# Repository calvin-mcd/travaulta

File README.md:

# travaultas

The travaultas are a series of EC (topre) pcbs for mechvault's [Vault35](https://mechvault.net/products/vault-35-mini-keyboard) series designed by calvin0563. 

The series consists of the HHKB and WKL pcbs, both supporting a single bottomrow layout with the double 1.75u splitbars, and the Number/Macropad, supporting all layout options. 

Firmware source code and the OEM plate file are available in their respective folders. In order to fit the topre pcb into the case, small modifications to some housings are necessary. Please refer to the extensive build guide by cia\_moonchild in order to learn how to make the assembled pcb fit into the vault35 case.

[Build Guide!!!](https://imgur.com/a/L5vGjtF)

**BEWARE**: The HHKB pcb has been fully tested and confirmed to work. The WKL and Numpad have not yet been prototyped and still require firmware. 

## Layout

**HHKB**

[Link](http://www.keyboard-layout-editor.com/#/gists/d333b15956554a98cf3ed6f06e2de3bf)

**WKL**

[Link](https://www.keyboard-layout-editor.com/#/gists/da6e12de7bd5171aa8982730b8f45f17)

**NUMPAD**

## Images

## Firmware

The basic EC firmware is ready to go and the source code is provided for tweaking any settings.

## Plates & Hardware

The plate file is OEM housing (so original, deskey, klc, pbb housings should all work). Be sure to order the plate in 1.2mm thickness regardless of material.

Furthermore, you will need 17x 10mm M2 screws and M2 nuts to assemble the HHKB and WKL pcbs. And 6x 10mm M2 screws and nuts to assemble numbpad.

## Disclaimer

1) Please proceed with caution with respect to copyright issues when using this repository
2) Take note that this is strictly for non-commercial use only
3) This PCB has been fully tested and confirmed to work. The members of the PCB development team are however not liable if you end up with a non-functional pcb. Order at your own risk. Support will not be provided but pull requests will be reviewed and possibly accepted.

## License

Shield: 

This work is licensed under a  
[Creative Commons Attribution-NonCommercial-ShareAlike 4.0 International License](http://creativecommons.org/licenses/by-nc-sa/4.0/).

## Credits

big thanks go out to Cain both for the inspiration and the support! My topre work is heavily lifted of Cipulot\#8455's open source work. I could not have done it without these resources. So I want to thank both cipulot and matthewdias\#2671 for their direct input, feedback and help along the way. Much much appreciated!

So many other thanks to go around, I fear I will forget people. There is Ciantha with their amazing guide! A whole bunch of early supporters that made the proto order possible. The keyboard Atelier discord for support. ssbb\#9052 with help with the firmware! And finally Alas/Sofia who decided to get a first GB for this on its feet!!

Any questions, contact Calvin0563 on Discord.

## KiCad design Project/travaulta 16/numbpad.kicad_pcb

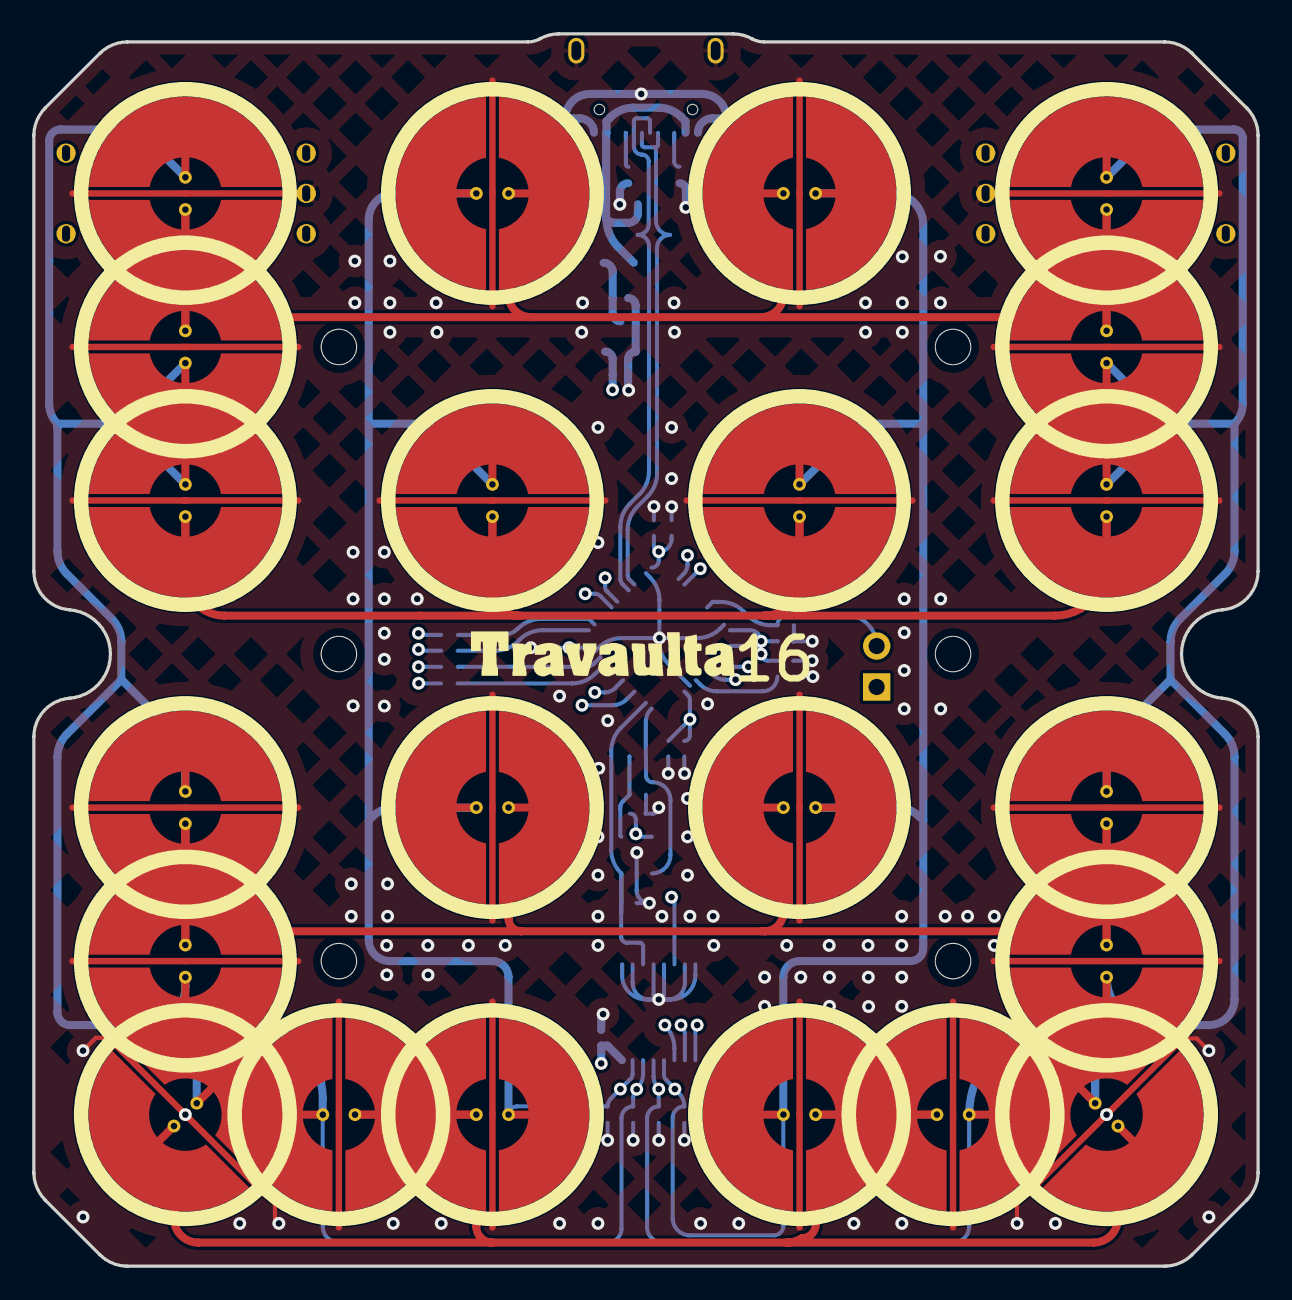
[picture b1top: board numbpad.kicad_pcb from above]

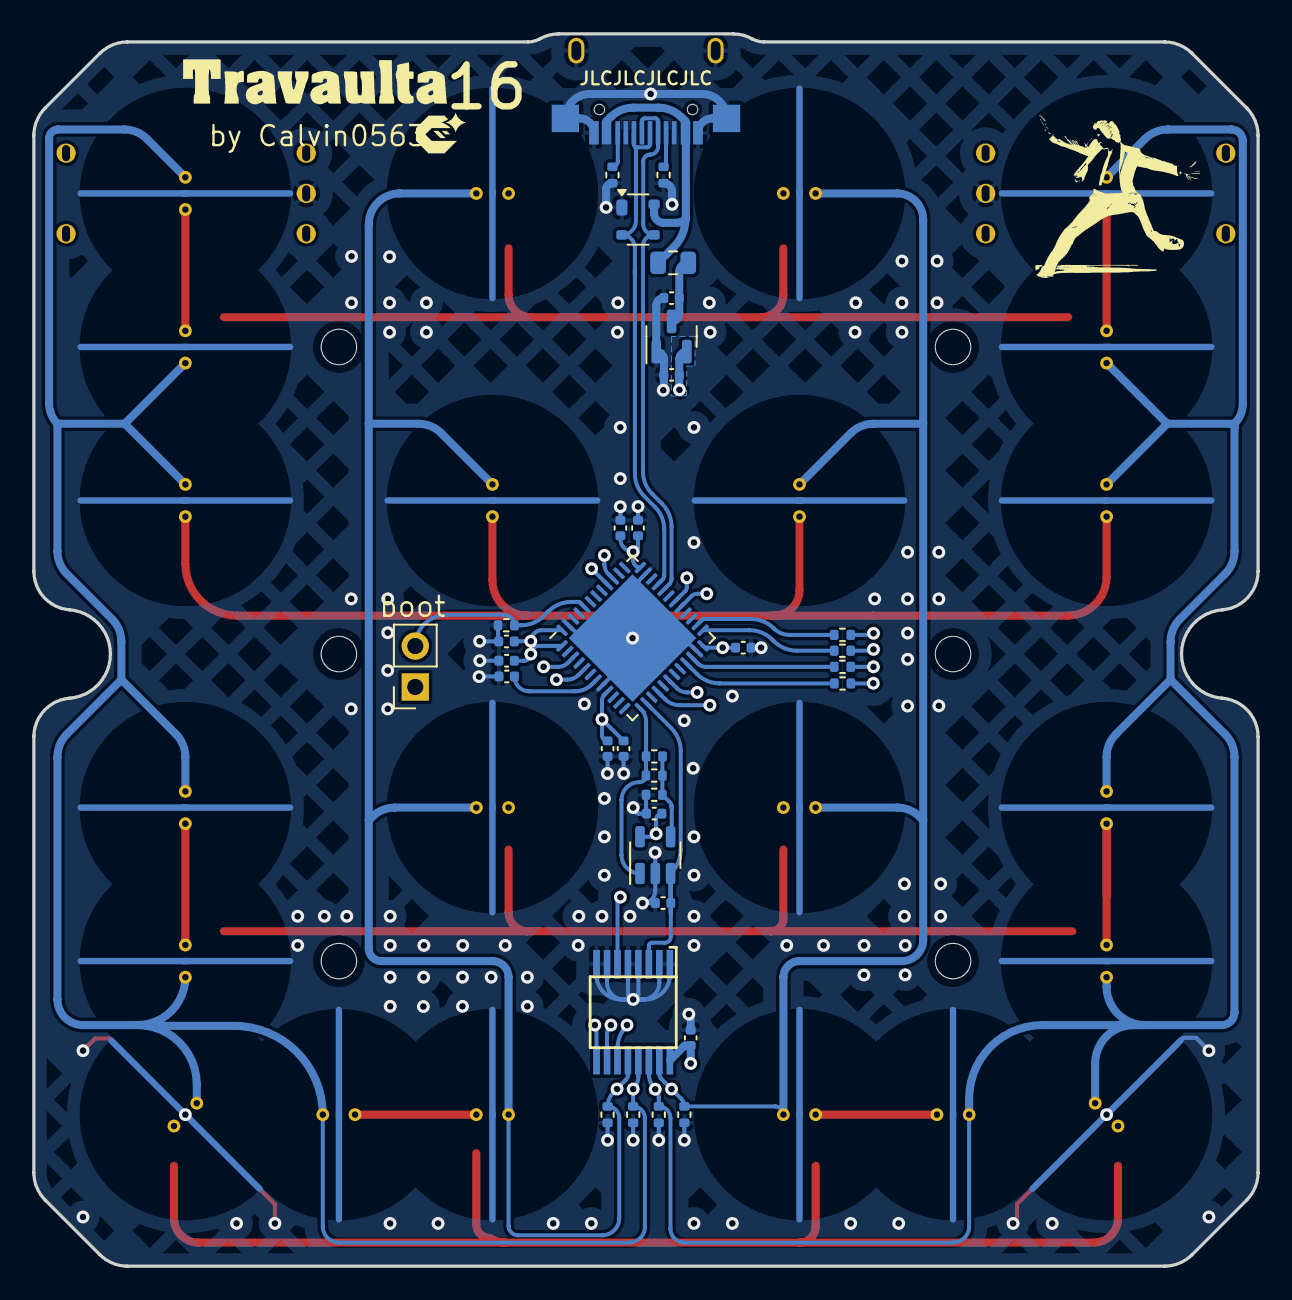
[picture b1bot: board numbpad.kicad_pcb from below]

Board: 4 copper layers, 76.0 x 76.5 mm, 63 parts (41 on the bottom side), 33 nets.

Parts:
C1, C2, C3, C4, C5, C7: 100nf; C_0402_1005Metric
C6: 10uF; C_0402_1005Metric
C8: 1uF; C_0402_1005Metric
C9, C10: 100nF; C_0402_1005Metric
C11: 220pF NP0; C_0402_1005Metric
C_LDO1, C_LDO2: 1uF; C_0402_1005Metric
F1: 500mA; Fuse_0805_2012Metric
H1, H2, H3, H4, H5, H6: MountingHole; HOLE_M2
R1: 10k; R_0402_1005Metric
R2, R3, R4, R5: 100; R_0402_1005Metric
R6, R7, R8, R9, R11: 100k; R_0402_1005Metric
R12: 1k; R_0402_1005Metric
R13: DNP; R_0402_1005Metric
R_USB1, R_USB2: 5.1k; R_0402_1005Metric
SW1, SW2, SW3, SW4, SW5, SW6, SW7, SW8, SW9, SW10, SW11, SW12, SW13, SW14, SW15, SW16, SW18, SW19, SW21, SW22: EC_SW; ecs_pad_1U_no_ring
SW17: SKQGABE010; PinSocket_1x02_P2.54mm_Vertical
SW20, SW23: EC_SW_RotaryEncoder_Switch; ecs_pad_1U_no_ring_rotary_encoder_ec12
U1: STM32F072CBUx; QFN-48-1EP_7x7mm_P0.5mm_EP5.6x5.6mm
U2: PRTR5V0U2X; SOT-143
U3: XC6206PxxxMR; SOT-23
U4: 74HC4051; TSSOP16
U5: OPA354; SOT-23-5
USB1: HRO-TYPE-C-31-M-12; XUNPU-TYPEC-312DSS-ACP16-Assembly

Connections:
+3V3: C2.1, C3.1, C4.1, C5.1, C6.1, C7.1, C8.1, C9.2, C10.2, C_LDO2.1, SW17.1, U1.1 (VBAT), U1.9 (VDDA), U1.24 (VDD), U1.36 (VDDIO2), U1.48 (VDD), U3.2 (VO), U4.16 (VCC), U5.5 (V+)
+5V: C_LDO1.1, F1.2, U3.3 (VI)
ADC: R11.1, R13.1, U1.13 (PA3), U5.1
AMUX_SEL_0: U1.16 (PA6), U4.11 (S0)
AMUX_SEL_1: U1.18 (PB0), U4.10 (S1)
AMUX_SEL_2: U1.3 (PC14), U4.9 (S2)
APLEX_EN_PIN_0: U1.5 (PF0), U4.6 (~E)
APLEX_OUT: C11.1, U1.14 (PA4), U4.3 (A), U5.3 (+)
BOOT0: R1.1, SW17.2, U1.44 (BOOT0)
Col 0: R8.1, SW1.1, SW5.1, SW9.1, SW13.1, SW18.1, SW20.2, SW22.1, U4.14 (A1)
Col 1: R6.1, SW2.1, SW6.1, SW10.1, SW14.1, U4.15 (A2)
Col 2: R9.1, SW3.1, SW7.1, SW11.1, SW15.1, U4.12 (A3)
Col 3: R7.1, SW4.1, SW8.1, SW12.1, SW16.1, SW19.1, SW21.1, SW23.1, U4.13 (A0)
D+: U1.33 (PA12), U2.2 (I/O1), USB1.6 (DP1), USB1.8 (DP2)
D-: U1.32 (PA11), U2.3 (I/O2), USB1.5 (DN2), USB1.7 (DN1)
GND: C1.2, C2.2, C3.2, C4.2, C5.2, C6.2, C7.2, C8.2, C9.1, C10.1, C11.2, C_LDO1.2, C_LDO2.2, R1.2, R6.2, R7.2, R8.2, R9.2, R12.2, R_USB1.2, R_USB2.2, SW1.3 (SG), SW2.3 (SG), SW3.3 (SG), SW4.3 (SG), SW5.3 (SG), SW6.3 (SG), SW7.3 (SG), SW8.3 (SG), SW9.3 (SG), SW10.3 (SG), SW11.3 (SG), SW12.3 (SG), SW13.3 (SG), SW14.3 (SG), SW15.3 (SG), SW16.3 (SG), SW18.3 (SG), SW19.3 (SG), SW20.3, SW20.C, SW21.3 (SG), SW22.3 (SG), SW23.3, SW23.C, U1.8 (VSSA), U1.23 (VSS), U1.35 (VSS), U1.47 (VSS), U1.49 (VSS), U2.1 (GND), U3.1 (GND), U4.1 (A4), U4.2 (A6), U4.4 (A7), U4.5 (A5), U4.7 (VEE), U4.8 (GND), U5.2 (V-), USB1.1 (GND), USB1.12 (GND), USB1.13 (SHIELD)
NRST: C1.1, U1.7 (NRST)
unnamed: R3.1, U1.21 (PB10)
unnamed: R2.1, U1.22 (PB11)
unnamed: R4.1, U1.25 (PB12)
unnamed: R5.1, U1.26 (PB13)
unnamed: R11.2, R12.1, R13.2, U5.4 (-)
unnamed: R_USB1.1, USB1.4 (CC1)
unnamed: R_USB2.1, USB1.10 (CC2)
Row 0: R4.2, SW2.2, SW3.2, SW18.2, SW19.2, SW20.1, SW23.2
Row 1: R5.2, SW5.2, SW6.2, SW7.2, SW8.2
Row 2: R2.2, SW1.2, SW9.2, SW10.2, SW11.2, SW12.2, SW21.2
Row 3: R3.2, SW4.2, SW13.2, SW14.2, SW15.2, SW16.2, SW22.2
VCC: F1.1, U2.4 (VCC), USB1.2 (VBUS), USB1.11 (VBUS)
rotA: SW20.A, U1.30 (PA9)
rotB: SW20.B, U1.29 (PA8)
rotC: SW23.A, U1.39 (PB3)
rotD: SW23.B, U1.40 (PB4)

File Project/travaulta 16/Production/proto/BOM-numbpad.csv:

Comment,Designator,Footprint,LCSC
1k,R12,R_0402_1005Metric,C11702
OPA354,U5,SOT-23-5,C13388
220pF NP0,C11,C_0402_1005Metric,C1530
100,"R2,R3,R4,R5",R_0402_1005Metric,C25076
100k,"R11,R6,R7,R8,R9",R_0402_1005Metric,C25741
10k,R1,R_0402_1005Metric,C25744
5.1k,"R_USB1,R_USB2",R_0402_1005Metric,C25905
PRTR5V0U2X,U2,SOT-143,C2827688
500mA,F1,Fuse_0805_2012Metric,C2833485
HRO-TYPE-C-31-M-12,USB1,XUNPU-TYPEC-312DSS-ACP16-Assembly,C2909601
100nf,"C1,C10,C2,C3,C4,C5,C7,C9",C_0402_1005Metric,C307331
10uF,C6,C_0402_1005Metric,C315248
1uF,"C8,C_LDO1,C_LDO2",C_0402_1005Metric,C52923
XC6206PxxxMR,U3,SOT-23,C5446
74HC4051,U4,TSSOP16,C5645
STM32F072CBUx,U1,QFN-48-1EP_7x7mm_P0.5mm_EP5.6x5.6mm,C92504

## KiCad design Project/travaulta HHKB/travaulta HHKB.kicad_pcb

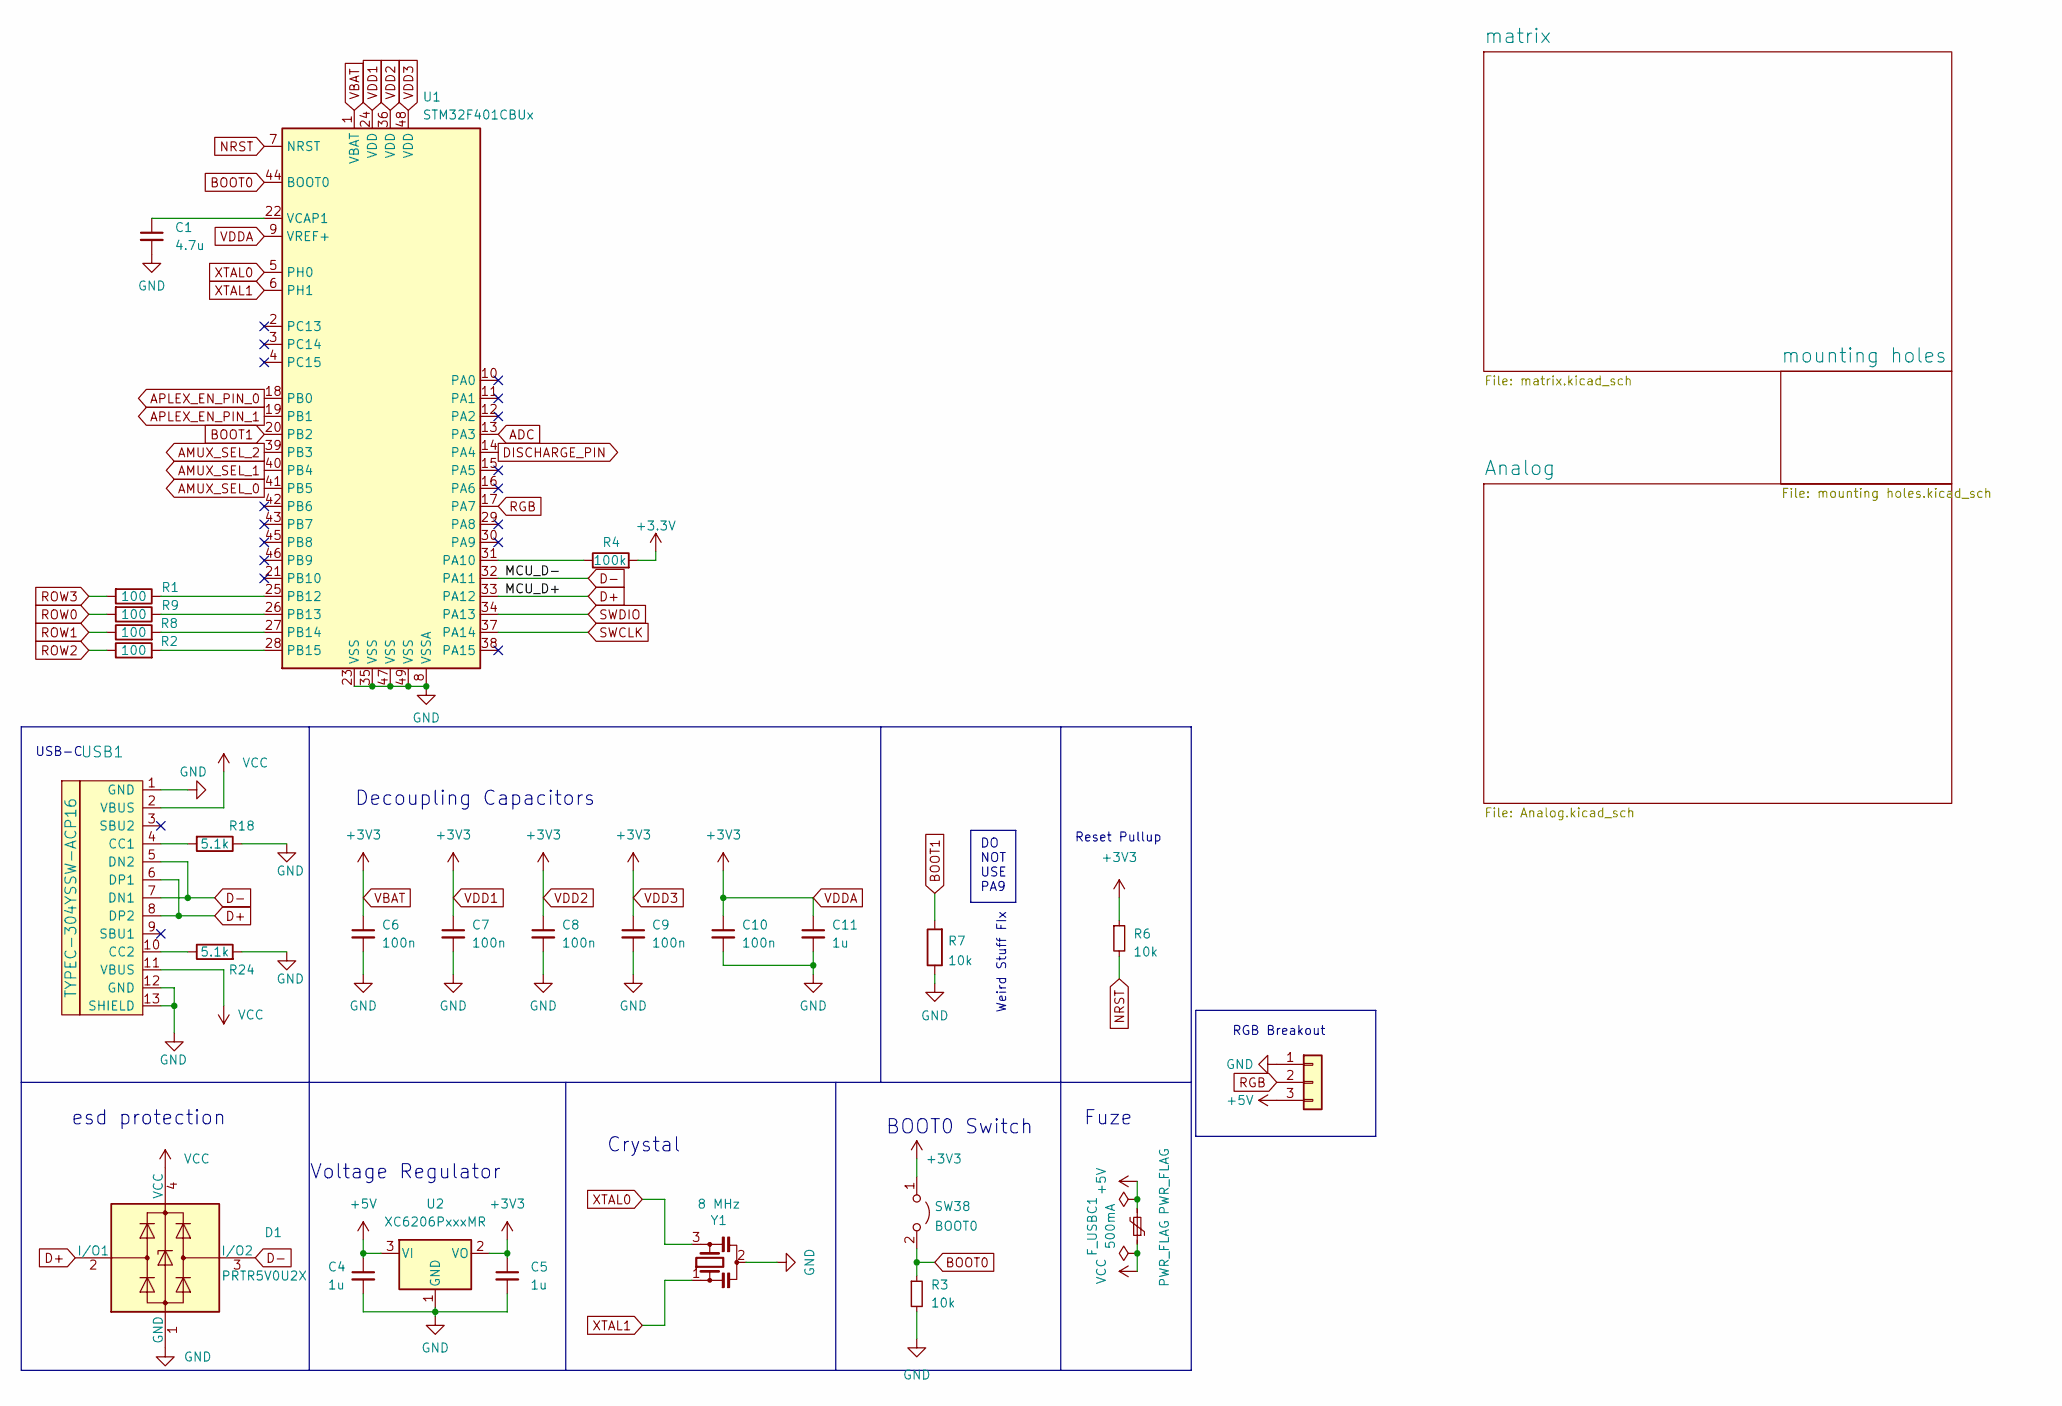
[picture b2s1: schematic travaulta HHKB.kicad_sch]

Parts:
C1: 4.7u; C_0402_1005Metric
C4, C5, C11: 1u; C_0402_1005Metric
C6, C7, C8, C9, C10: 100n; C_0402_1005Metric
D1: PRTR5V0U2X; SOT-143
F_USBC1: 500mA; Fuse_1206_3216Metric
J5: ARGB; PinHeader_1x03_P1.27mm_Vertical
R1, R2, R8, R9: 100; R_0402_1005Metric; LCSC C25076
R3, R6: 10k; R_0402_1005Metric
R4: 100k; R_0402_1005Metric; LCSC C25741
R7: 10k; R_0402_1005Metric; LCSC C25744
R18, R24: 5.1k; R_0402_1005Metric; LCSC C25905
SW38: BOOT0; PinHeader_1x02_P2.54mm_Vertical
U1: STM32F401CBUx; QFN-48-1EP_7x7mm_P0.5mm_EP5.6x5.6mm; LCSC C118825
U2: XC6206PxxxMR; SOT-23
USB1: TYPEC-304YSSW-ACP16; LCSC C2840392
Y1: 8 MHz; Resonator_SMD_Murata_CSTxExxV-3Pin_3.0x1.1mm; LCSC C907975

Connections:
+5V: C4.1, F_USBC1.2, U2.3 (VI); also elsewhere on the board
ADC: U1.13 (PA3); also elsewhere on the board
AMUX_SEL_0: U1.41 (PB5); also elsewhere on the board
AMUX_SEL_1: U1.40 (PB4); also elsewhere on the board
AMUX_SEL_2: U1.39 (PB3); also elsewhere on the board
APLEX_EN_PIN_0: U1.18 (PB0); also elsewhere on the board
APLEX_EN_PIN_1: U1.19 (PB1); also elsewhere on the board
APLEX_OUT_PIN_0: U1.14 (PA4); also elsewhere on the board
BOOT0: R3.1, SW38.2 (B), U1.44 (BOOT0)
BOOT1: R7.2, U1.20 (PB2)
D+: D1.2 (I/O1), U1.33 (PA12), USB1.6 (DP1), USB1.8 (DP2)
D-: D1.3 (I/O2), U1.32 (PA11), USB1.5 (DN2), USB1.7 (DN1)
NRST: R6.2, U1.7 (NRST)
unnamed: R4.1, U1.31 (PA10)
unnamed: R9.1, U1.26 (PB13)
unnamed: R8.2, U1.27 (PB14)
unnamed: R2.2, U1.28 (PB15)
unnamed: C1.1, U1.22 (VCAP1)
unnamed: R18.2, USB1.4 (CC1)
unnamed: R24.1, USB1.10 (CC2)
RGB: U1.17 (PA7); also elsewhere on the board
ROW0: R9.2; also elsewhere on the board
ROW1: R8.1; also elsewhere on the board
ROW2: R2.1; also elsewhere on the board
SWCLK: U1.37 (PA14)
SWDIO: U1.34 (PA13)
VCC: D1.4 (VCC), F_USBC1.1, USB1.2 (VBUS), USB1.11 (VBUS)
XTAL0: U1.5 (PH0), Y1.3
XTAL1: U1.6 (PH1), Y1.1

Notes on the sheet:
Weird Stuff FIx
BOOT0 Switch
USB-C
RGB Breakout
Voltage Regulator
Reset Pullup
esd protection
DO NOT USE PA9
Fuze
Crystal
Decoupling Capacitors

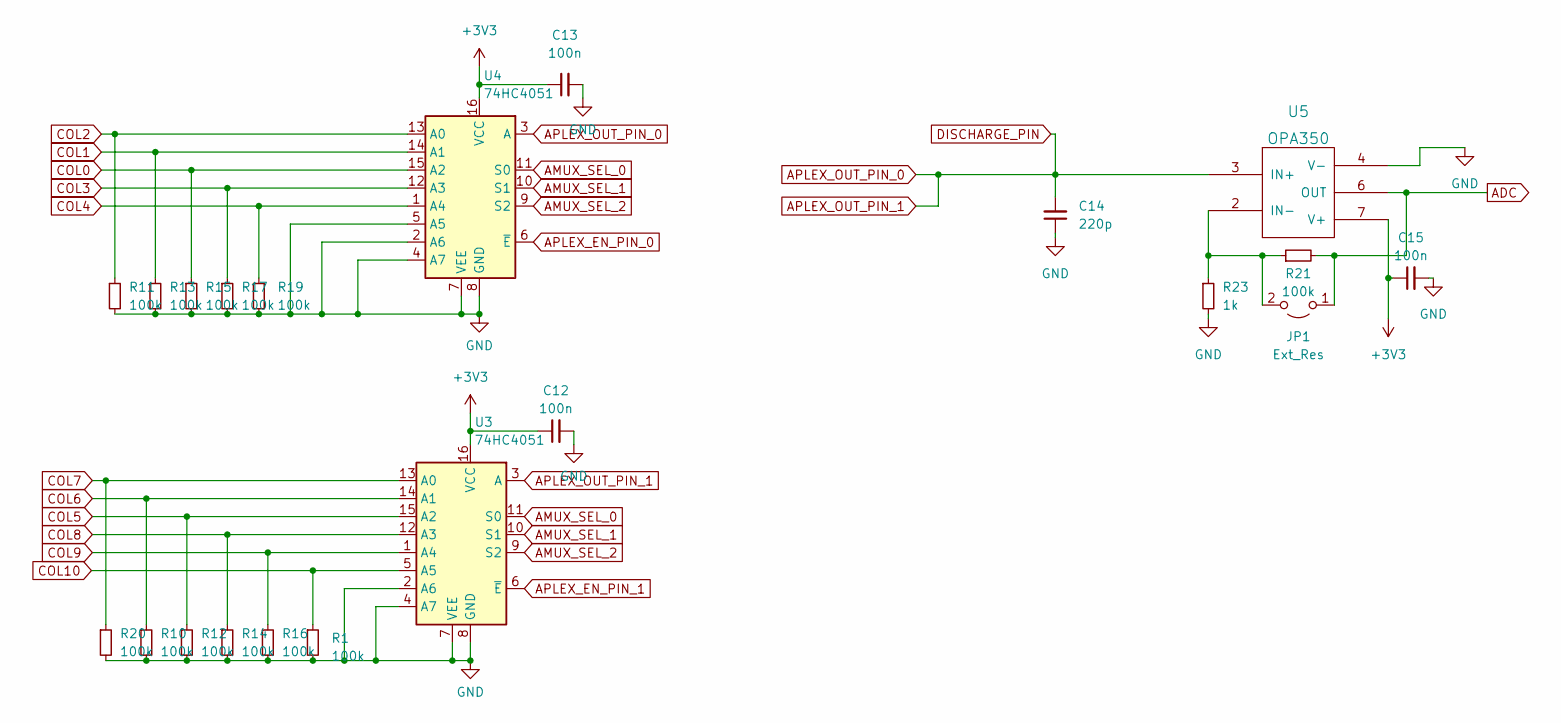
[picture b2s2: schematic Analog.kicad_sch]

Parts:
C12, C13, C15: 100n; C_0402_1005Metric
C14: 220p; C_0402_1005Metric
JP1: Ext_Res; R_0603_1608Metric_Pad0.98x0.95mm_HandSolder
R1, R10, R11, R12, R13, R14, R15, R16, R17, R19, R20, R21: 100k; R_0402_1005Metric
R23: 1k; R_0402_1005Metric
U3, U4: 74HC4051; TSSOP16
U5: OPA350; SOIC-8_3.9x4.9mm_P1.27mm

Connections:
ADC: JP1.1 (A), R21.2, U5.6 (OUT); also elsewhere on the board
AMUX_SEL_0: U3.11 (S0), U4.11 (S0); also elsewhere on the board
AMUX_SEL_1: U3.10 (S1), U4.10 (S1); also elsewhere on the board
AMUX_SEL_2: U3.9 (S2), U4.9 (S2); also elsewhere on the board
APLEX_EN_PIN_0: U4.6 (~E); also elsewhere on the board
APLEX_EN_PIN_1: U3.6 (~E); also elsewhere on the board
APLEX_OUT_PIN_0: C14.2, U3.3 (A), U4.3 (A), U5.3 (IN+); also elsewhere on the board
COL0: R15.1, U4.15 (A2); also elsewhere on the board
COL1: R13.1, U4.14 (A1); also elsewhere on the board
COL2: R11.1, U4.13 (A0); also elsewhere on the board
COL3: R17.1, U4.12 (A3); also elsewhere on the board
COL4: R19.1, U4.1 (A4); also elsewhere on the board
COL5: R12.1, U3.15 (A2); also elsewhere on the board
COL6: R10.1, U3.14 (A1); also elsewhere on the board
COL7: R20.1, U3.13 (A0); also elsewhere on the board
COL8: R14.1, U3.12 (A3); also elsewhere on the board
COL9: R16.1, U3.1 (A4); also elsewhere on the board
unnamed: JP1.2 (B), R21.1, R23.1, U5.2 (IN-)

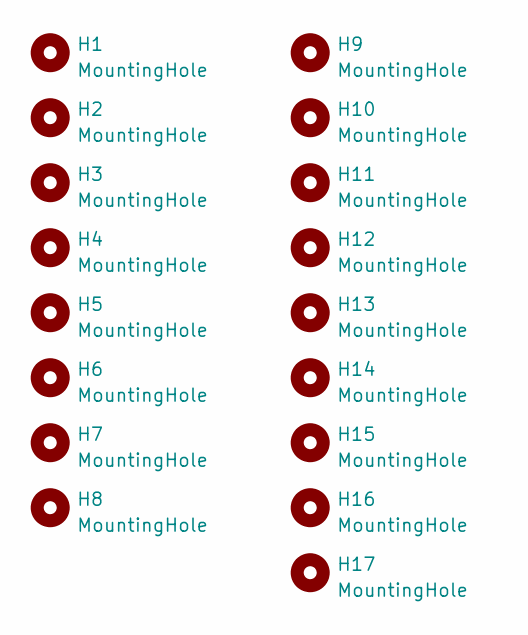
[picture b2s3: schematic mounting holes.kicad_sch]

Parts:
H1, H2, H3, H4, H5, H6, H7, H8, H9, H10, H11, H12, H13, H14, H15, H16, H17: MountingHole; HOLE_M2

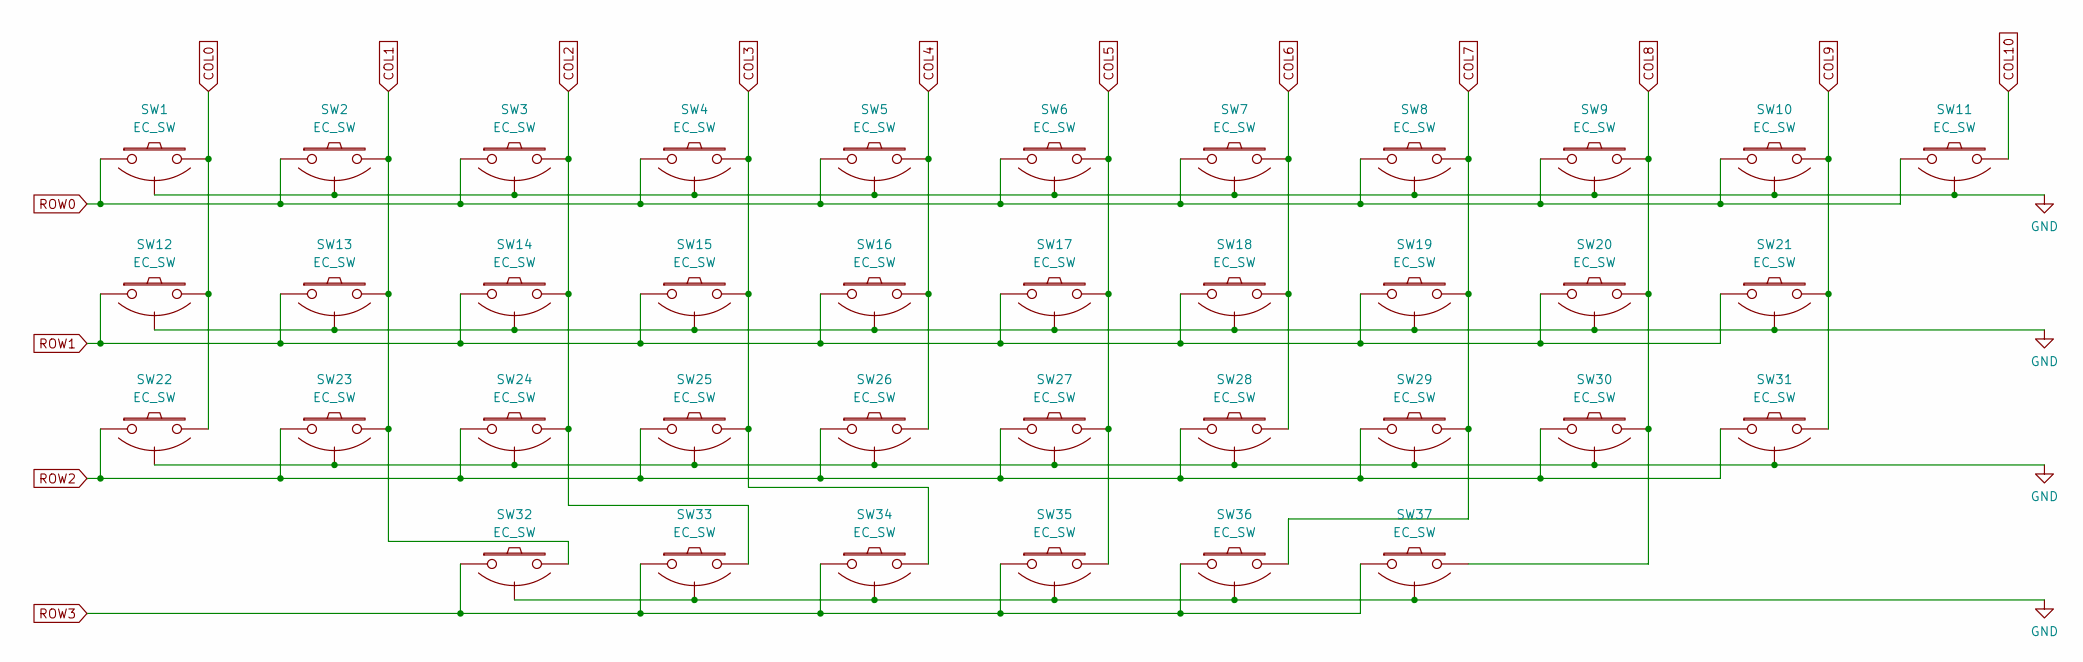
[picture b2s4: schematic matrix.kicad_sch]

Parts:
SW1, SW2, SW3, SW4, SW5, SW6, SW7, SW8, SW9, SW10, SW11, SW12, SW13, SW14, SW15, SW16, SW17, SW18, SW19, SW20, SW21, SW22, SW23, SW24, SW25, SW26, SW27, SW28, SW29, SW30, SW31, SW32, SW33, SW34, SW35, SW36, SW37: EC_SW; ecs_pad_1U_no_ring

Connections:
COL0: SW1.2, SW12.2, SW22.2; also elsewhere on the board
COL1: SW2.2, SW13.2, SW23.2, SW32.2; also elsewhere on the board
COL2: SW3.2, SW14.2, SW24.2, SW33.2; also elsewhere on the board
COL3: SW4.2, SW15.2, SW25.2, SW34.2; also elsewhere on the board
COL4: SW5.2, SW16.2, SW26.2; also elsewhere on the board
COL5: SW6.2, SW17.2, SW27.2, SW35.2; also elsewhere on the board
COL6: SW7.2, SW18.2, SW28.2; also elsewhere on the board
COL7: SW8.2, SW19.2, SW29.2, SW36.2; also elsewhere on the board
COL8: SW9.2, SW20.2, SW30.2, SW37.2; also elsewhere on the board
COL9: SW10.2, SW21.2, SW31.2; also elsewhere on the board
ROW0: SW1.1, SW2.1, SW3.1, SW4.1, SW5.1, SW6.1, SW7.1, SW8.1, SW9.1, SW10.1, SW11.1; also elsewhere on the board
ROW1: SW12.1, SW13.1, SW14.1, SW15.1, SW16.1, SW17.1, SW18.1, SW19.1, SW20.1, SW21.1; also elsewhere on the board
ROW2: SW22.1, SW23.1, SW24.1, SW25.1, SW26.1, SW27.1, SW28.1, SW29.1, SW30.1, SW31.1; also elsewhere on the board

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
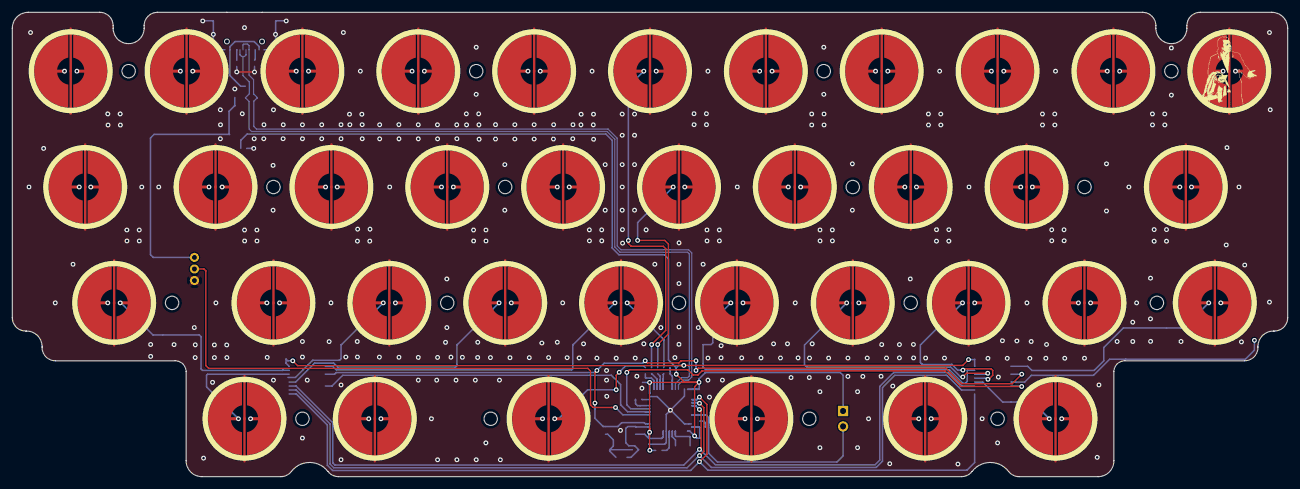
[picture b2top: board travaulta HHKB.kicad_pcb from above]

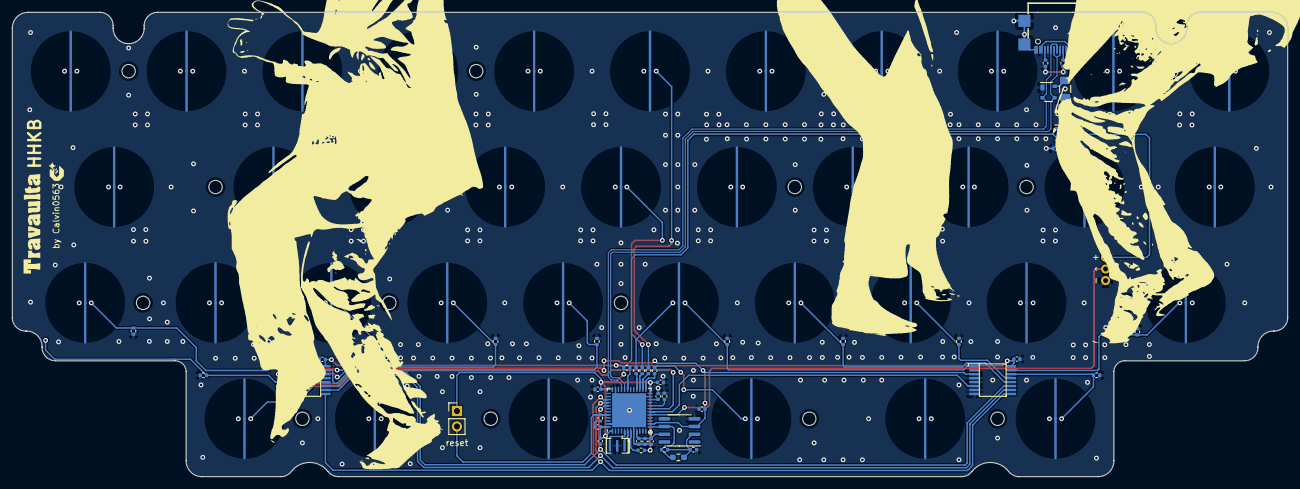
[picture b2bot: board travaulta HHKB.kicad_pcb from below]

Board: 4 copper layers, 209.7 x 76.4 mm, 102 parts (47 on the bottom side), 43 nets.

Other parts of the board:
J1: ARGB; PinHeader_1x03_P1.27mm_Vertical
R5: 100k; R_0402_1005Metric

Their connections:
+5V: J1.3; also elsewhere on the board
RGB: J1.2; also elsewhere on the board

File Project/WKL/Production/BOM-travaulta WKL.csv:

Comment,Designator,Footprint,LCSC
1k,R23,R_0402_1005Metric,C11702
STM32F401CBUx,U1,QFN-48-1EP_7x7mm_P0.5mm_EP5.6x5.6mm,C118825
OPA350,U5,SOIC-8_3.9x4.9mm_P1.27mm,C13388
220p,C14,C_0402_1005Metric,C1530
4.7u,C1,C_0402_1005Metric,C23733
100,"R1,R2,R8,R9",R_0402_1005Metric,C25076
100k,"R10,R11,R12,R13,R14,R15,R16,R17,R19,R20,R21,R4,R5",R_0402_1005Metric,C25741
10k,"R3,R6,R7",R_0402_1005Metric,C25744
5.1k,"R18,R24",R_0402_1005Metric,C25905
PRTR5V0U2X,D1,SOT-143,C2827688
TYPEC-304YSSW-ACP16,USB1,XUNPU-TYPEC-312DSS-ACP16-Assembly,C2840392
100n,"C10,C12,C13,C15,C6,C7,C8,C9",C_0402_1005Metric,C307331
1u,"C11,C4,C5",C_0402_1005Metric,C52923
XC6206PxxxMR,U2,SOT-23,C5446
74HC4051,"U3,U4",TSSOP16,C5645
500mA,F_USBC1,Fuse_1206_3216Metric,C70076
8 MHz,Y1,Resonator_SMD_Murata_CSTxExxV-3Pin_3.0x1.1mm,C907975
Ext_Res,JP1,R_0603_1608Metric_Pad0.98x0.95mm_HandSolder,

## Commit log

2023-01-29 schematics
2023-01-29 switch footprints plaed
2023-01-30 analog schematics added
    some questions
2023-01-30 backup
2023-01-31 autosave
2023-02-02 question marker
2023-02-04 changed rol, col schematics /// made pcb 4 layers
2023-02-06 early routing
2023-02-12 component placement
2023-02-13 component placement, some basic silkscreen prep
2023-02-14 routing work
2023-02-14 created simplified version
2023-02-16 cleaned pcb, silkscreen, created first plates
2023-02-17 created more plates
2023-02-18 clean up folders, edit silkscreen
2023-02-19 silkscreen work
2023-02-20 plate cutouts
    needs plate edge cut
2023-02-21 first draft plates complete
2023-02-23 rgb attempt
2023-02-23 first rough rgb version done
    no idea about interferences and all.
2023-03-02 production files
2023-03-04 MCU swap, UCB components moved, crystal swap
2023-03-10 clean up
2023-03-13 changed reset button, new production files
2023-03-21 fresh production files
2023-04-01 rerouting matrix to fix error
    shifting around a bunch of switches, ending up with hopefully functional but not pretty routing
2023-04-01 backup project edited for alternative matrix fix
2023-04-02 Revert "backup"
    This reverts commit cce0f1319d57ca5dfebc02d32957ad5213dbdb00.
2023-04-02 one pin matrix fix
2023-04-07 new production files
2023-04-13 edited preliminary firmware, small routing cleanups
2023-04-14 clean up, new zip. backups
2023-04-15 tried to export dxf edge cut with all screw holes
2023-04-17 small schematic error fixed
2023-05-02 revision started
2023-05-03 revision routing
2023-05-04 rerouting in progress
2023-05-04 tiny rerouting
2023-05-05 GND via revision
2023-05-06 revision routing further improved (edge problems addressed)
2023-05-07 small tweaks
2023-05-07 error check = 0
2023-05-11 reset button simplified
2023-05-14 prototype files, fresh gerbers
2023-05-15 fresh gerbers
    deleted old plate gerbers, need new export
2023-05-17 pcb clean up, fresh gerbers
2023-05-19 backups
2023-05-31 readme names added
2023-06-07 cleaning up folder
2023-06-13 project cleanup
2023-06-14 disclaimer update & backup
2023-06-30 backup
    some small DRC checks, all checks out okay!
2023-08-01 silkscreen labelling changed for GB
2023-08-02 fresh set of production files
2023-08-20 created plate files
2023-08-29 fresh gerbers, production files
2023-09-14 added WKL version (yet to be tested)
2023-09-24 wkl production files
2023-11-09 plate files updated, new production files
2023-11-17 added rgb breakout to HHKB&WKL
2023-12-02 small cosmetic updates
2023-12-16 renamed rgb to hhkb for clarity
2024-01-19 fresh gerbers WKL, backup
2024-01-31 changed rgb pin on HHKB&WKL for better compatibility
2024-02-09 fresh gerbers for HHKB WKL
2024-04-21 plate update
2024-05-13 fresh gerbers WKL
2024-06-10 publish
2024-06-10 cleanup
2024-08-05 plate work
2024-08-07 added fresh plate files
2025-03-01 added WKL & numpad
2025-09-22 added naevies plate for hhkb
